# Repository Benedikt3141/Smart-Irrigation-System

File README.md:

→ Current Version as .step Assembly ([Assembly](src/assembly_and_models/SmartIrrigationSystem-Assembly.step)

# About

The Smart Irrigation System is a battery-powered monitoring and control system for watering up to six individual plants.

Each plant is monitored by a capacitive soil moisture sensor connected to the main control unit.

The project currently focuses on the main monitoring and control unit. A separate watering unit is planned but not fully designed yet. Communication between both units is intended to use ESP-NOW.

## Project Overview

The system consists of two main parts:

### Main Monitoring and Control Unit

The main unit collects sensor data, displays current measurements on a TFT screen, logs data to an SD card and indicates the system status using an LED strip.

Each soil moisture sensor is connected individually using an audio jack connector.

### Watering Unit

The watering unit is planned as a separate module. It will receive commands from the main control unit via ESP-NOW and control the water flow using a solenoid valve.
The unit should also monitor the water tank level using an ultrasonic sensor.

This part of the system is still work in progress. But It will be bareable with electronic modules I have at hand so I won't need a custom PCB for it and it also doesn't count to the sponsorship.

## Feature overview

###### Sensors (Inputs)

- **Soil mositure monitoring** for individual plants
- **Temperature**
- Humidity
- Air pressure
- Air Quality
- CO2 concentration
- Solar intensity
- 3 Buttons
- *Tank fill state sensor*

###### Other features and outputs

- **Battery powered**
- 3.2" TFT LCD Screen with resistive touch
- Buzzer
- SD log with data saved as .csv
- LED-Strip status indicator
- Lighting for the Buttons
- magnetic valve for watering Control
- *web interface*
- *Push Emails when water is empty/error etc.*

   → Version one of this project (didn't completely work)

## Repository Structure

This repository contains both the firmware and the PCB design files.

- `/firmware/` contains the PlatformIO firmware project.
- `/firmware/src/` contains the ESP32 source code.
- `/src/pcb/` contains the KiCad PCB design files.
- `/src/pcb/Smart_Irrigation_SystemV2/production/` contains the exported Gerber files for manufacturing.
- `/src/pcb/assembly_and_models` contains 3d assembly files

## File Structure

```
Smart-Irrigation-System/
├── firmware/
├── images/
├── src/│  
│   ├── assembly_and_models/
│   │   ├── SmartIrrigationSystem-Assembly.step
│   │   └── SmartIrrigationSystem.FCStd
│   └── pcb/
│       └── Smart_Irrigation_SytemV2/
├── .gitignore
├── BOM.csv
├── Concept.jpg
├── JOURNAL.md
├── LICENSE
├── README.md
├── cart_adafruit.png
├── cart_amazon.png
└── cart_jlcpcb.png
```

## Getting started

#### Requirements

To work with this project, you need:

* VS Code
* PlatformIO or pioarduino IDE Extension
* C++ Compiler
* KiCad 10.0.1 or later
* You also need a 3D printer with Filament you want to use for printing the housing and other regular hardware tools like a soldering iron 

#### Installation

Use git to clone this repository into your computer.

```
git clone https://github.com/Benedikt3141/Smart-Irrigation-System.git
```

Open the project folder in VS Code and build/upload the firmware using PlatformIO or pioarduino IDE.

###### Hardware

You can either use the provided Gerber files or modify the KiCad project and generate new manufacturing files for your preferred PCB supplier.

You can find the gerberfiles for JLCPCB [here ](src/pcb/Smart_Irrigation_SystemV2/production). The correlating `BOM.csv` and `position.csv` can be found in the same directories.

## License

[MIT](https://choosealicense.com/licenses/mit/)

## Current Project Status

This project is still in development.

The main monitoring unit is mostly implemented. The watering unit, web interface and notification system are planned but not finished yet.

## Sources

[MQ2 Library](https://github.com/labay11/MQ-2-sensor-library/)
[SD Card](https://RandomNerdTutorials.com/esp32-web-server-microsd-card/)

## Why I think I should receive financial sponsorship for this project

I already received $180 in rewards from Hack Club in July 2026. Since then, I have spent nearly 100 hours working on this project. During this time, I have gained many new skills and a lot of knowledge in PCB design, including effective routing techniques, reading datasheets, organizing schematics, and working with Git. I have also developed personal skills, especially resilience and perseverance throughout this long process.

I started this project seven months ago, and I'm still determined to bring it to completion. Even though I've had to pause my work several times because I'm still in school, have exams coming up in two years, and have many other hobbies and responsibilities that take up my free time, I've always found a way to keep making progress.

I've carefully reviewed and checked my design multiple times, and I'm now quite confident that the hardware design is ready to be finalized.

I'm really proud of what I've accomplished and everything I've learned along the way. This project has been a challenging but incredibly rewarding experience, and I'm excited to take the next step toward completing it.

Thank you, Hack Club, for supporting my previous request. I would be very grateful if you could help me with this next chapter of my project! I need 500$ (450€) to finance this the new pcb (SmartIrrigationSystemV2.5) and the other neccessary parts mentioned in the BOM like Displays, fans, buttons, LEDs etc.. The rest of the money I'll need for this project iteration I'll pay from my own money.

## AI Usage

All of the code was written by myself. Since this is a work in progress, the code may still contain bugs or parts that could be improved.

The PCB design, hardware architecture and  the firmware were
created completely by myself.

## Bill of Materials (BOM)

| Item                                                            | Qty | Unit price | Total price | Purchase link                                                  | Notes                                                      |
| ----------------------------------------------------------------- | ----: | -----------: | ------------: | ---------------------------------------------------------------- | ------------------------------------------------------------ |
| PCB_Board                                                       |   1 |       15€ |        15€ |[Product](cart_jlcpcb.png)                                                             | —                                                         |
| PCB_Assembly                                                    |   1 |      186€ |       186€ | [Product](cart_jlcpcb.png)                                                            | —                                                         |
| PCB Shipping and Taxes                                          |   1 |      100€ |       100€ | [Product](cart_jlcpcb.png)                                                             | Last time I ordered, I had to pay 60€ tax before delivery |
| Nocuta NF-A6x15 5V PWM                                          |   1 |       17€ |        17€ | [Product](https://www.amazon.de/dp/B0DJP3987K?tag=noctua09-21) | Fan                                                        |
| 3.2 TFT Display with Resistive Touchscreen                      |   2 |       15€ |        30€ | [Product](https://www.adafruit.com/product/4278)               | Touchscreen                                                |
| Kailh Mechanical Key Switches - Tactile Brown - 10-pack WS2812B |   1 |        7€ |         7€ | [Product](https://www.adafruit.com/product/4954)               | Switches                                                   |
| NeoPixel Nano 2020 RGB LEDs -10-Pack -WS2812B                   |   1 |        4€ |         4€ | [Product](https://www.adafruit.com/product/4684)               | LEDs for under the switches                                |
| NeoPixel Stick -8 x 5050 RGBW LEDs -WarmWhite ~3000K            |   2 |        8€ |        16€ | [Product](https://www.adafruit.com/product/2867)               | LEDs for under the board                                   |
| Translucent Keycaps for MX Compatible Switches - 10 pack        |   1 |        5€ |         5€ | [Product](https://www.adafruit.com/product/4956)               | Keycaps                                                    |
| Lithium Ion Polymer Battery - 3.7v 2500mAh                      |   1 |       15€ |        15€ | [Product](https://www.adafruit.com/product/328)                | LiPo                                                       |
| SoilMoisture Sensors 6pcs                      |   1 |       9€ |        9€ | [Product](https://www.amazon.de/Aideepen-Bodenfeuchtigkeitssensor-Hygrometer-Modul-korrosionsbest%C3%A4ndiges-Arduin0-Pflanzenbew%C3%A4sserung/dp/B08GCRZVSR/ref=sr_1_4?s=industrial)                | Moisture sensors                                                        |
| Shipping                                                        |   1 |       50€ |        50€ | —                                                             | Shipping from Adafruit and Amazon                          |

**Total: 454 €**

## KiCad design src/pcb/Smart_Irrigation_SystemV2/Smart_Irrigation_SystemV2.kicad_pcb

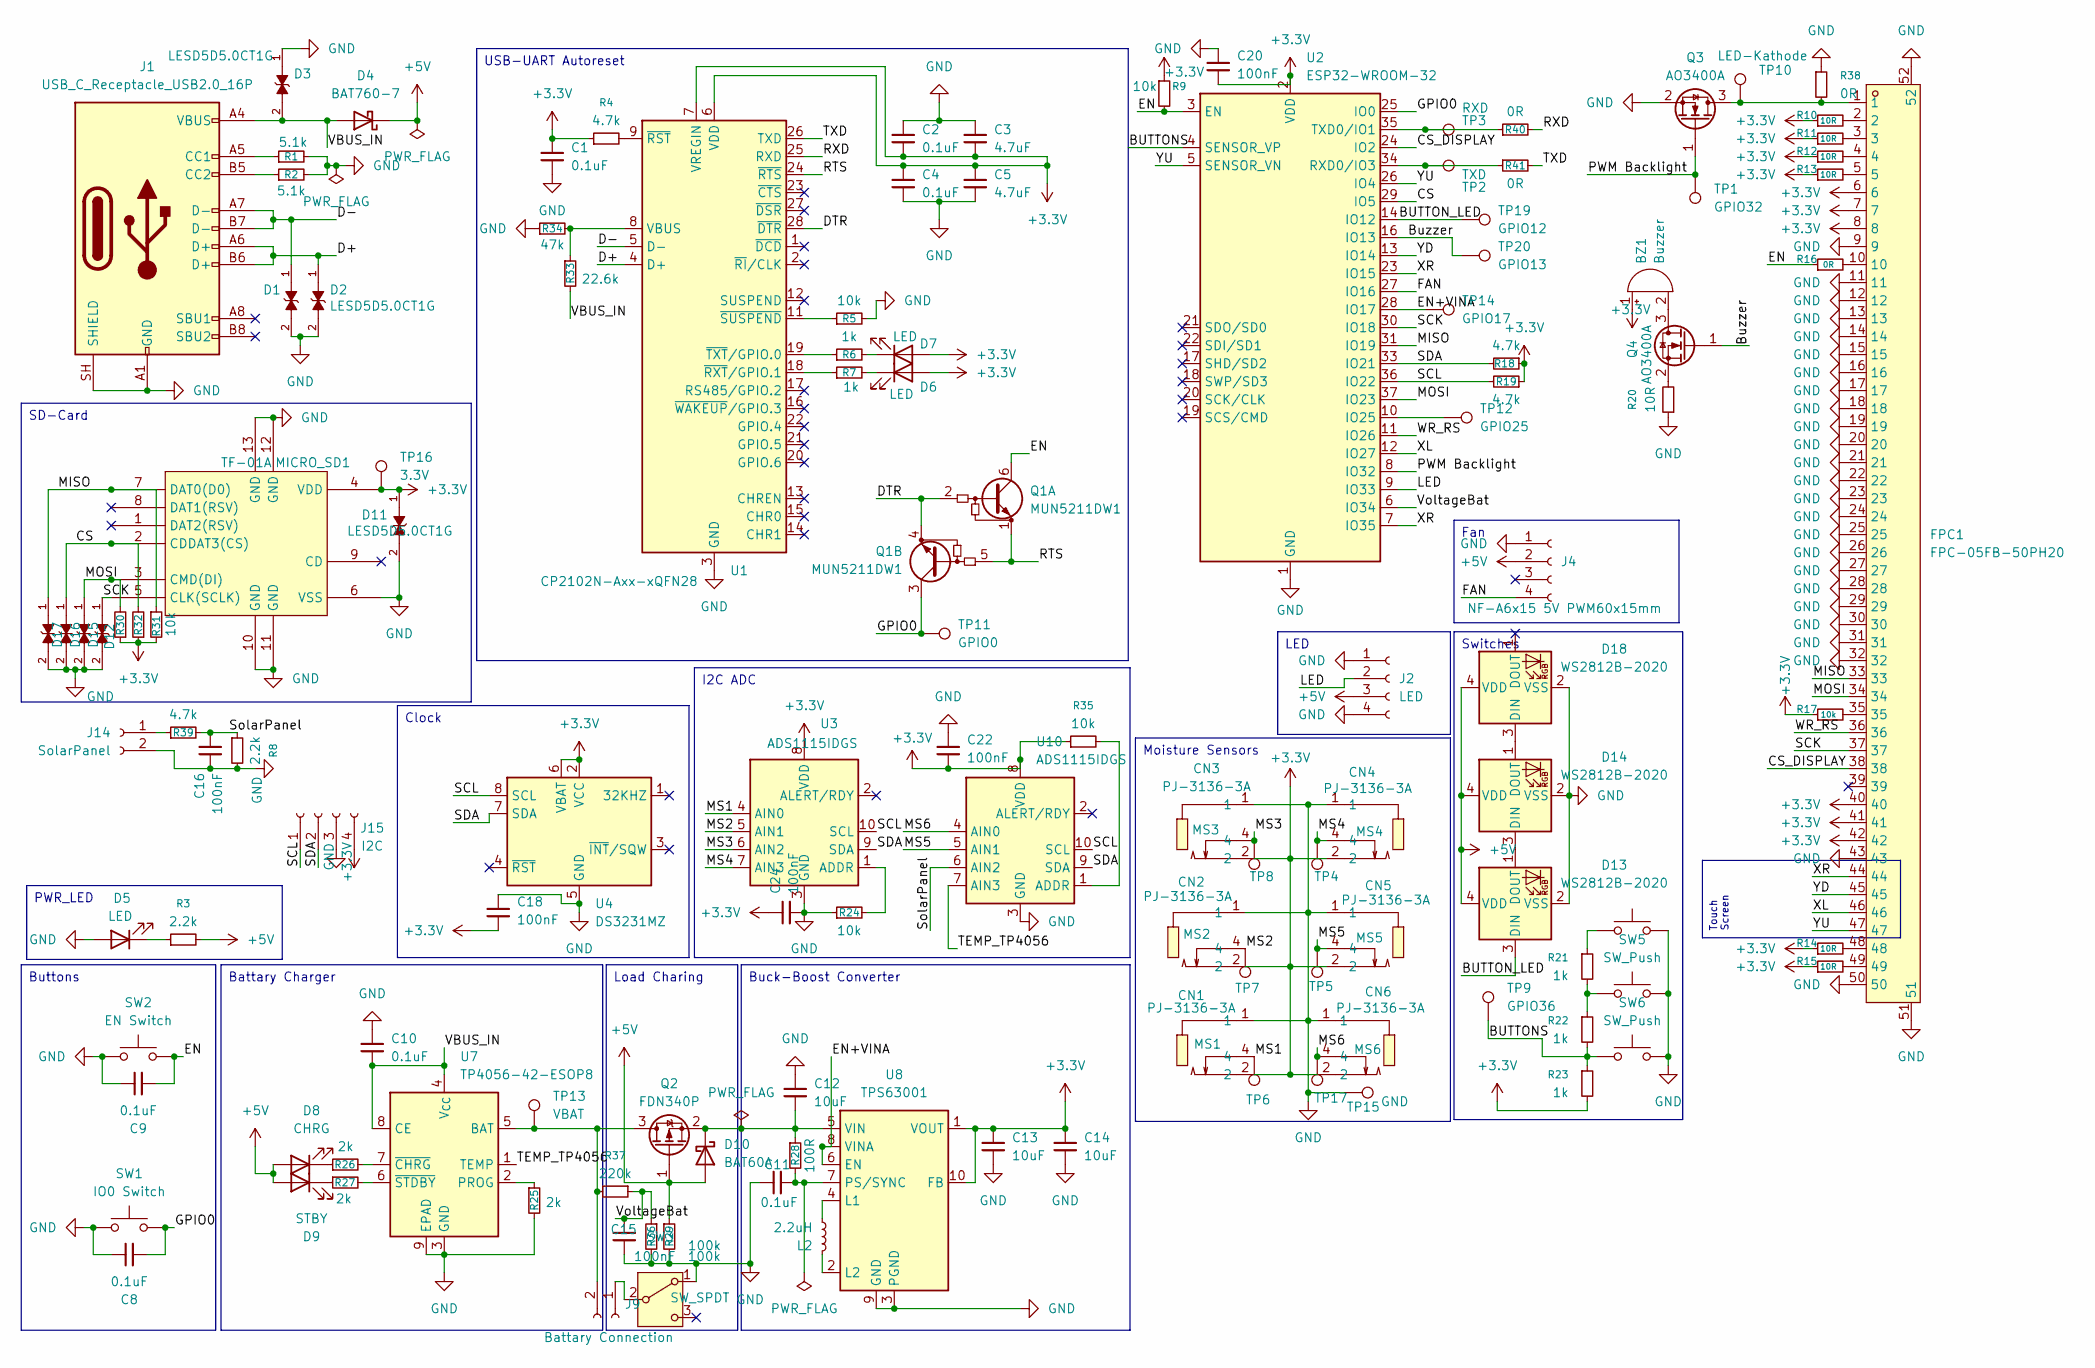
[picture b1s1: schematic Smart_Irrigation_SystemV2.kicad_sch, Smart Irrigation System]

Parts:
BZ1: Buzzer; BUZ-TH_BD12.0-P6.50-D0.6-FD; JLCPCB Part Number C968749
C1, C2, C4, C8, C9, C10, C11: 0.1uF; C_0805_2012Metric; JLCPCB Part Number C28233
C3, C5: 4.7uF; C_0805_2012Metric; JLCPCB Part Number C1779
C12, C13, C14: 10uF; C_0805_2012Metric; JLCPCB Part Number C15850
C15, C16, C18, C20, C22, C24: 100nF; C_0805_2012Metric; JLCPCB Part Number C29926
CN1, CN2, CN3, CN4, CN5, CN6: PJ-3136-3A; AUDIO-TH_PJ-3136-3A; MPN PJ-3136-3A; LCSC Part C707248
D1, D2, D3, D11, D12, D15, D16, D17: LESD5D5.0CT1G; TVS_LESD5D5.0CT1G; PARTREV O; JLCPCB Part Number C5274290
D4: BAT760-7; D_SOD-323; JLCPCB Part Number C27636120
D5, D6, D7: LED; D_0603_1608Metric; JLCPCB Part Number C2286
D8: CHRG; D_0603_1608Metric; JLCPCB Part Number C2287
D9: STBY; D_0603_1608Metric; JLCPCB Part Number C12624
D10: BAT60A; D_SOD-323; JLCPCB Part Number C513277
D13, D14, D18: WS2812B-2020; LED_WS2812B-2020_PLCC4_2.0x2.0mm
FPC1: FPC-05FB-50PH20; FPC-SMD_50P-P0.50_FPC-05FB-50PH20; MPN FPC-05FB-50PH20; LCSC Part C2856838
J1: USB_C_Receptacle_USB2.0_16P; USB_C_Receptacle_HCTL_HC-TYPE-C-16P-01A; JLCPCB Part Number C5337088
J2: LED; PinSocket_1x04_P2.54mm_Vertical
J4: NF-A6x15 5V PWM60x15mm; PinSocket_1x04_P2.54mm_Vertical
J9: Battary Connection; JST_PH_B2B-PH-K_1x02_P2.00mm_Vertical
J14: SolarPanel; JST_PH_B2B-PH-K_1x02_P2.00mm_Vertical
J15: I2C; PinSocket_1x04_P2.54mm_Vertical
L2: 2.2uH; IND-SMD_L6.6-W6.6; JLCPCB Part Number C128686
MICRO_SD1: TF-01A; TF-SMD_TF-01A; MPN TF-01A; JLCPCB Part Number C91145
Q1: MUN5211DW1; SOT-363_SC-70-6; JLCPCB Part Number C152507
Q2: FDN340P; SOT-23; JLCPCB Part Number C347510
Q3, Q4: AO3400A; SOT-23; JLCPCB Part Number C20917
R1, R2: 5.1k; R_0805_2012Metric; JLCPCB Part Number C26023
R3, R8: 2.2k; R_0805_2012Metric; JLCPCB Part Number C17520
R4, R18, R19, R39: 4.7k; R_0805_2012Metric; JLCPCB Part Number C17673
R5, R9, R17, R24, R30, R31, R32, R35: 10k; R_0805_2012Metric; JLCPCB Part Number C17414
R6, R7, R21, R22, R23: 1k; R_0805_2012Metric; JLCPCB Part Number C17513
R10, R11, R12, R13, R14, R15, R20: 10R; R_0805_2012Metric; JLCPCB Part Number C17415
R16, R38: 0R; R_0805_2012Metric; JLCPCB Part Number C17477
R25, R26, R27: 2k; R_0805_2012Metric; JLCPCB Part Number C17604
R28: 100R; R_0805_2012Metric; JLCPCB Part Number C17408
R29, R36: 100k; R_0805_2012Metric; JLCPCB Part Number C25611
R33: 22.6k; R_0805_2012Metric; JLCPCB Part Number C12825
R34: 47k; R_0805_2012Metric; JLCPCB Part Number C17713
R37: 220k; R_0805_2012Metric; JLCPCB Part Number C17556
R40, R41: 0R; R_1206_3216Metric; JLCPCB Part Number C17888
SW1: IO0 Switch; KEY-SMD_4P-L6.0-W6.0-P3.90-LS9.0; JLCPCB Part Number C83206
SW2: EN Switch; KEY-SMD_4P-L6.0-W6.0-P3.90-LS9.0; JLCPCB Part Number C83206
SW3: SW_SPDT; SW_100SP1T1B1M1QEH
SW4, SW5, SW6: SW_Push; KEY-TH_CPG1511F01S0X
TP1: GPIO32; TestPoint_Pad_D1.5mm
TP2: TXD; TestPoint_Pad_D1.5mm
TP3: RXD; TestPoint_Pad_D1.5mm
TP4: MS4; TestPoint_Pad_D1.5mm
TP5: MS5; TestPoint_Pad_D1.5mm
TP6: MS1; TestPoint_Pad_D1.5mm
TP7: MS2; TestPoint_Pad_D1.5mm
TP8: MS3; TestPoint_Pad_D1.5mm
TP9: GPIO36; TestPoint_Pad_D1.5mm
TP10: LED-Kathode; TestPoint_Pad_D1.5mm
TP11: GPIO0; TestPoint_Pad_D1.5mm
TP12: GPIO25; TestPoint_Pad_D1.0mm
TP13: VBAT; TestPoint_Pad_D1.5mm
TP14: GPIO17; TestPoint_Pad_D1.0mm
TP15: GND; TestPoint_Pad_2.5x2.5mm
TP16: 3.3V; TestPoint_Pad_2.5x2.5mm
TP17: MS6; TestPoint_Pad_D1.5mm
TP19: GPIO12; TestPoint_Pad_D1.0mm
TP20: GPIO13; TestPoint_Pad_D1.0mm
U1: CP2102N-Axx-xQFN28; QFN-28-1EP_5x5mm_P0.5mm_EP3.35x3.35mm; JLCPCB Part Number C964632
U2: ESP32-WROOM-32; JLCPCB Part Number C701343
U3, U10: ADS1115IDGS; TSSOP-10_3x3mm_P0.5mm; JLCPCB Part Number C37593
U4: DS3231MZ; SOIC-8_3.9x4.9mm_P1.27mm; JLCPCB Part Number C107410
U7: TP4056-42-ESOP8; SOIC-8-1EP_3.9x4.9mm_P1.27mm_EP2.41x3.3mm_ThermalVias; JLCPCB Part Number C16581
U8: TPS63001; Texas_DRC0010J_ThermalVias; JLCPCB Part Number C28060

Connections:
+3.3V: BZ1.1 (+), C1.1, C2.2, C3.2, C4.1, C5.1, C13.1, C14.1, C18.2, C20.2, C22.2, C24.1, CN1.2, CN2.2, CN3.2, CN4.2, CN5.2, CN6.2, D6.2 (A), D7.2 (A), D11.1, FPC1.6, FPC1.7, FPC1.8, FPC1.40, FPC1.41, FPC1.42, J15.4, MICRO_SD1.4 (VDD), R4.1, R9.1, R10.1, R11.1, R12.1, R13.1, R14.1, R15.1, R17.1, R18.1, R19.1, R23.2, R30.1, R31.2, R32.1, R35.1, TP16.1 (1_1), U1.6 (VDD), U1.7 (VREGIN), U2.2 (VDD), U3.8 (VDD), U4.2 (VCC), U4.6 (VBAT), U8.1 (VOUT), U8.10 (FB), U10.8 (VDD)
+5V: D4.1 (K), D8.2 (A), D9.2 (A), D10.2 (A), D13.4 (VDD), D14.4 (VDD), D18.4 (VDD), J2.3, J4.2, Q2.1 (G), R3.2, R29.1
/BUTTONS: R22.2, R23.1, SW6.1, TP9.1 (1_1), U2.4 (SENSOR_VP)
/BUTTON_LED: D13.3 (DIN), TP19.1 (1_1), U2.14 (IO12)
/Buzzer: Q4.1 (G), TP20.1 (1_1), U2.16 (IO13)
/CS: D16.1, MICRO_SD1.2 (CDDAT3(CS)), R32.2, U2.29 (IO5)
/CS_DISPLAY: FPC1.38, U2.24 (IO2)
/D+: D2.1, J1.A6 (D+), J1.B6 (D+), U1.4 (D+)
/D-: D1.1, J1.A7 (D-), J1.B7 (D-), U1.5 (D-)
/DTR: Q1.2 (B1), Q1.4 (E2), U1.28 (~DTR)
/EN: C9.2, Q1.6 (C1), R9.2, R16.1, SW2.2, U2.3 (EN)
/EN+VINA: TP14.1 (1_1), U2.28 (IO17), U8.6 (EN), U8.8 (VINA)
/FAN: J4.4, U2.27 (IO16)
/GPIO0: C8.2, Q1.3 (C2), SW1.2, TP11.1 (1_1), U2.25 (IO0)
/LED: J2.2, U2.9 (IO33)
/MISO: D17.1, FPC1.33, MICRO_SD1.7 (DAT0(D0)), R31.1, U2.31 (IO19)
/MOSI: D15.1, FPC1.34, MICRO_SD1.3 (CMD(DI)), R30.2, U2.37 (IO23)
/MS1: CN1.4, TP6.1 (1_1), U3.4 (AIN0)
/MS2: CN2.4, TP7.1 (1_1), U3.5 (AIN1)
/MS3: CN3.4, TP8.1 (1_1), U3.6 (AIN2)
/MS4: CN4.4, TP4.1 (1_1), U3.7 (AIN3)
/MS5: CN5.4, TP5.1 (1_1), U10.5 (AIN1)
/MS6: CN6.4, TP17.1 (1_1), U10.4 (AIN0)
/PWM Backlight: Q3.1 (G), TP1.1 (1_1), U2.8 (IO32)
/RTS: Q1.1 (E1), Q1.5 (B2), U1.24 (~RTS)
/RXD: R40.2, U1.25 (RXD)
/SCK: D12.1, FPC1.37, MICRO_SD1.5 (CLK(SCLK)), U2.30 (IO18)
/SCL: J15.1, R19.2, U2.36 (IO22), U3.10 (SCL), U4.8 (SCL), U10.10 (SCL)
/SDA: J15.2, R18.2, U2.33 (IO21), U3.9 (SDA), U4.7 (SDA), U10.9 (SDA)
/SolarPanel: C16.1, R8.1, R39.2, U10.6 (AIN2)
/TEMP_TP4056: U7.1 (TEMP), U10.7 (AIN3)
/TXD: R41.2, U1.26 (TXD)
/VBUS_IN: C10.2, D3.2, D4.2 (A), J1.A4 (VBUS), J1.A9 (VBUS), J1.B4 (VBUS), J1.B9 (VBUS), R33.2, U7.4 (V_{CC}), U7.8 (CE)
/VoltageBat: C15.1, R36.1, R37.1, U2.6 (IO34)
/WR_RS: FPC1.36, U2.11 (IO26)
/XL: FPC1.46, U2.12 (IO27)
/XR: FPC1.44, U2.7 (IO35), U2.23 (IO15)
/YD: FPC1.45, U2.13 (IO14)
/YU: FPC1.47, U2.5 (SENSOR_VN), U2.26 (IO4)
GND: C1.2, C2.1, C3.1, C4.2, C5.2, C8.1, C9.1, C10.1, C11.1, C12.1, C13.2, C14.2, C15.2, C16.2, C18.1, C20.1, C22.1, C24.2, CN1.1, CN2.1, CN3.1, CN4.1, CN5.1, CN6.1, D1.2, D2.2, D3.1, D5.2 (A), D11.2, D12.2, D13.2 (VSS), D14.2 (VSS), D15.2, D16.2, D17.2, D18.2 (VSS), FPC1.9, FPC1.11, FPC1.12, FPC1.13, FPC1.14, FPC1.15, FPC1.16, FPC1.17, FPC1.18, FPC1.19, FPC1.20, FPC1.21, FPC1.22, FPC1.23, FPC1.24, FPC1.25, FPC1.26, FPC1.27, FPC1.28, FPC1.29, FPC1.30, FPC1.31, FPC1.32, FPC1.43, FPC1.50, FPC1.51, FPC1.52, J1.A1 (GND), J1.A12 (GND), J1.B1 (GND), J1.B12 (GND), J1.SH (SHIELD), J2.1, J2.4, J4.1, J14.2, J15.3, MICRO_SD1.6 (VSS), MICRO_SD1.10 (GND), MICRO_SD1.11 (GND), MICRO_SD1.12 (GND), MICRO_SD1.13 (GND), Q3.2 (S), R1.2, R2.2, R5.2, R8.2, R20.1, R24.1, R25.2, R29.2, R34.1, R36.2, R38.1, SW1.1, SW2.1, SW3.1 (A), SW4.2, SW5.2, SW6.2, TP15.1 (1_1), U1.3 (GND), U1.29 (GND), U2.1 (GND), U2.15 (GND), U2.38 (GND), U2.39 (GND), U3.3 (GND), U4.5 (GND), U7.3 (GND), U7.9 (EPAD), U8.3 (PGND), U8.9 (GND), U8.11 (PGND), U10.3 (GND)
unnamed: BZ1.2 (-), Q4.3 (D)
unnamed: D5.1 (K), R3.1
unnamed: D6.1 (K), R7.2
unnamed: D7.1 (K), R6.2
unnamed: D8.1 (K), R26.1
unnamed: D9.1 (K), R27.1
unnamed: C12.2, D10.1 (K), Q2.2 (S), R28.1, U8.5 (VIN)
unnamed: D13.1 (DOUT), D14.3 (DIN)
unnamed: D14.1 (DOUT), D18.3 (DIN)
unnamed: FPC1.2, R10.2
unnamed: FPC1.3, R11.2
unnamed: FPC1.4, R12.2
unnamed: FPC1.5, R13.2
unnamed: FPC1.10, R16.2
unnamed: FPC1.35, R17.2
unnamed: FPC1.48, R14.2
unnamed: FPC1.49, R15.2
unnamed: J1.A5 (CC1), R1.1
unnamed: J1.B5 (CC2), R2.1
unnamed: J9.1, SW3.2 (B)
unnamed: J9.2, Q2.3 (D), R37.2, TP13.1 (1_1), U7.5 (BAT)
unnamed: J14.1, R39.1
unnamed: FPC1.1, Q3.3 (D), R38.2, TP10.1 (1_1)
unnamed: Q4.2 (S), R20.2
unnamed: R21.1, SW4.1
unnamed: R21.2, R22.1, SW5.1
unnamed: R33.1, R34.2, U1.8 (VBUS)
unnamed: R4.2, U1.9 (~RST)
unnamed: R7.1, U1.18 (~RXT/GPIO.1)
unnamed: R5.1, U1.11 (~SUSPEND)
unnamed: R6.1, U1.19 (~TXT/GPIO.0)
unnamed: TP12.1 (1_1), U2.10 (IO25)
unnamed: R41.1, TP2.1 (1_1), U2.34 (RXD0/IO3)
unnamed: R40.1, TP3.1 (1_1), U2.35 (TXD0/IO1)
unnamed: R24.2, U3.1 (ADDR)
unnamed: R25.1, U7.2 (PROG)
unnamed: R26.2, U7.7 (~CHRG)
unnamed: R27.2, U7.6 (~STDBY)
unnamed: L2.1, U8.4 (L1)
unnamed: L2.2, U8.2 (L2)
unnamed: C11.2, R28.2, U8.7 (PS/SYNC)
unnamed: R35.2, U10.1 (ADDR)

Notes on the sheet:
USB-UART Autoreset
Battary Charger
Clock
PWR_LED
LED
Buck-Boost Converter
Switches
Touch Screen
Buttons
Moisture Sensors
I2C ADC
Fan
SD-Card
Load Charing

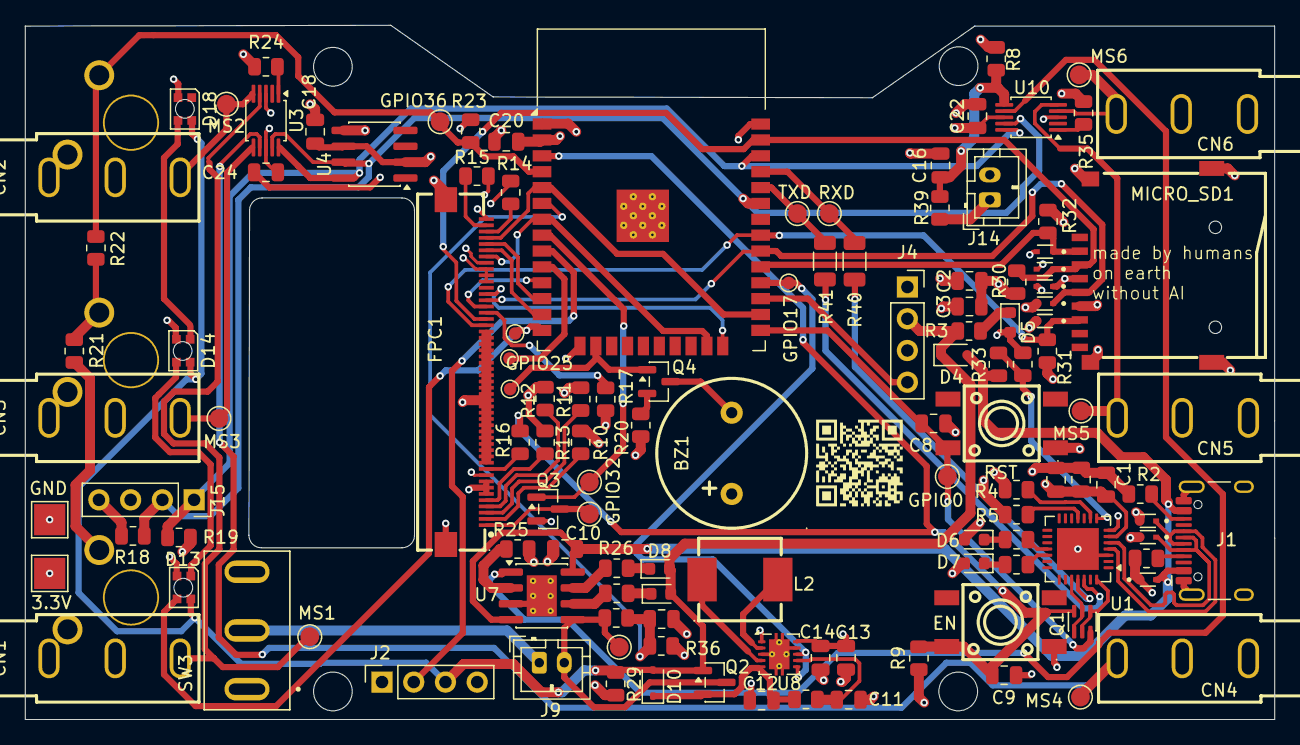
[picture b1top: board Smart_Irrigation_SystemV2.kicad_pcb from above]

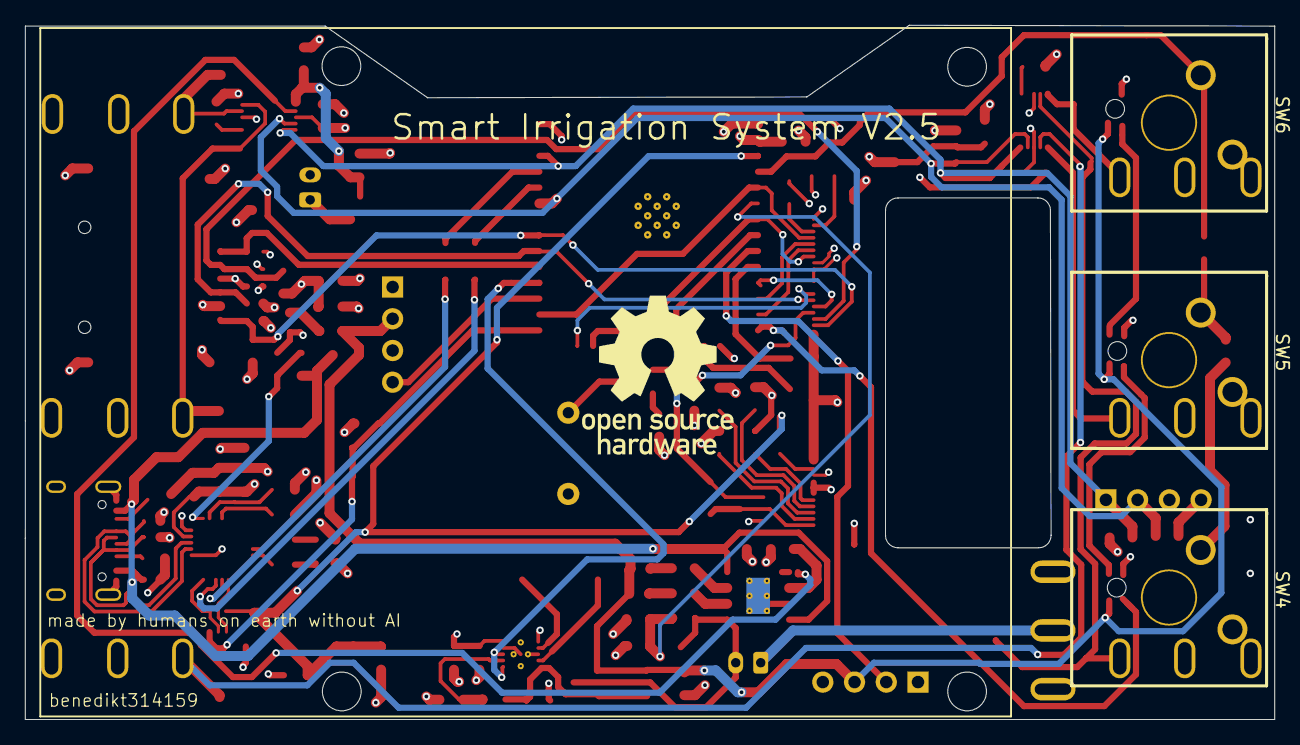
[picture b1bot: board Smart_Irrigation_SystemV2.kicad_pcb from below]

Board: 4 copper layers, 100.0 x 55.6 mm, 128 parts (3 on the bottom side), 82 nets.

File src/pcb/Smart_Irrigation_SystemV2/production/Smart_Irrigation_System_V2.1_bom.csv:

Designator,Footprint,Quantity,Value,LCSC Part #
"C1, C10, C11, C2, C4, C8, C9",0805,7,0.1uF,C28233
"C12, C13, C14",0805,3,10uF,C15850
"C15, C16, C18, C20, C21, C22, C23, C24",0805,8,100nF,C29926
"C3, C5, C6",0805,3,4.7uF,C1779
C7,0805,1,22uF,C45783
"CN1, CN2, CN3, CN4, CN5, CN6",AUDIO-TH_PJ-3136-3A,6,PJ-3136-3A,C707248
"D1, D11, D12, D15, D16, D17, D2, D3",TVS_LESD5D5.0CT1G,8,LESD5D5.0CT1G,C5274290
D10,D_SOD-323,1,BAT60A,C513277
D4,D_SOD-323F,1,BAT760-7,C27636120
"D5, D6, D7",0603,3,LED,C2286
D8,0603,1,CHRG,C2287
D9,0603,1,STBY,C12624
J1,USB_C_Receptacle_HCTL_HC-TYPE-C-16P-01A,1,USB_C_Receptacle_USB2.0_16P,C5337088
"J10, J11, J13, J15, J6",JST_EH_B4B-EH-A_1x04_P2.50mm_Vertical,5,I2C,
J14,JST_PH_B2B-PH-K_1x02_P2.00mm_Vertical,1,SolarPanel,
J16,PinSocket_1x04_P2.54mm_Vertical,1,GPIO_Expander,
J2,CON_5051105091_MOL,1,FPC_Connector,C779387
J9,JST_PH_B2B-PH-K_1x02_P2.00mm_Vertical,1,Battary Connection,
L1,IND-SMD_L7.1-W6.6,1,1uH,C726315
L2,IND-SMD_L6.6-W6.6,1,2.2uH,C128686
MICRO_SD1,TF-SMD_TF-01A,1,TF-01A,C91145
Q1,SOT-363_SC-70-6,1,MUN5211DW1,C152507
Q2,SOT-23,1,FDN340P,C347510
Q3,SOT-23,1,AO3400A,C20917
"R1, R2",0805,2,5.1k,C26023
"R10, R11, R12, R13, R14, R15",0805,6,10R,C17415
R16,0805,1,0R,C17477
"R17, R24, R30, R31, R32, R35, R5",0805,7,10k,C17414
"R18, R19, R39, R4",0805,4,4.7k,C17673
"R20, R21, R22, R23, R6, R7",0805,6,1k,C17513
"R25, R26, R27",0805,3,2k,C17604
R28,0805,1,100R,C17408
"R29, R36, R9",0805,3,100k,C25611
R3,0805,1,2.2k,C17520
R37,0805,1,220k,C17556
"R40, R41",1206,2,0R,C17888
R8,0805,1,453k,C17702
SW1,KEY-SMD_4P-L6.0-W6.0-P3.90-LS9.0,1,IO0 Switch,C83206
SW2,KEY-SMD_4P-L6.0-W6.0-P3.90-LS9.0,1,EN Switch,C83206
"SW3, SW4, SW5, SW6",SW_PUSH_6mm_H4.3mm,4,SW_Push,
TP1,TestPoint_Pad_D1.5mm,1,GPIO32,
TP10,TestPoint_Pad_D1.5mm,1,LED-Kathode,
TP11,TestPoint_Pad_D1.5mm,1,GPIO0,
TP13,TestPoint_Pad_D1.5mm,1,VBAT,
TP14,TestPoint_Pad_D1.5mm,1,GND,
TP15,TestPoint_Pad_2.5x2.5mm,1,GND,
TP16,TestPoint_Pad_4.0x4.0mm,1,3.3V,
TP17,TestPoint_Pad_D1.5mm,1,MS6,
TP18,TestPoint_Pad_D1.5mm,1,AnalogInput,
TP2,TestPoint_Pad_D1.5mm,1,TXD,
TP3,TestPoint_Pad_D1.5mm,1,RXD,
TP4,TestPoint_Pad_D1.5mm,1,MS4,
TP5,TestPoint_Pad_D1.5mm,1,MS5,
TP6,TestPoint_Pad_D1.5mm,1,MS1,
TP7,TestPoint_Pad_D1.5mm,1,MS2,
TP8,TestPoint_Pad_D1.5mm,1,MS3,
TP9,TestPoint_Pad_D1.5mm,1,GPIO36,
U1,QFN-28-1EP_5x5mm_P0.5mm_EP3.35x3.35mm,1,CP2102N-Axx-xQFN28,C964632 
"U10, U3",TSSOP-10_3x3mm_P0.5mm,2,ADS1115IDGS,C37593
U11,TSSOP-8_3x3mm_P0.65mm,1,PCA9536DP,C2649389
U2,ESP32-WROOM-32,1,ESP32-WROOM-32,C701343
U4,SOIC-8_3.9x4.9mm_P1.27mm,1,DS3231MZ,C107410
U5,SOT-563,1,TLV62568ADRL,C87122
U6,TSSOP-20_4.4x6.5mm_P0.65mm,1,SN74LVC245APW,C7848
U7,ESOP-8_L4.9-W3.9-P1.27-LS6.0-BL-EP,1,TP4056-42-ESOP8,C16581
U8,SOT-23-5,1,TPS63001,C28060

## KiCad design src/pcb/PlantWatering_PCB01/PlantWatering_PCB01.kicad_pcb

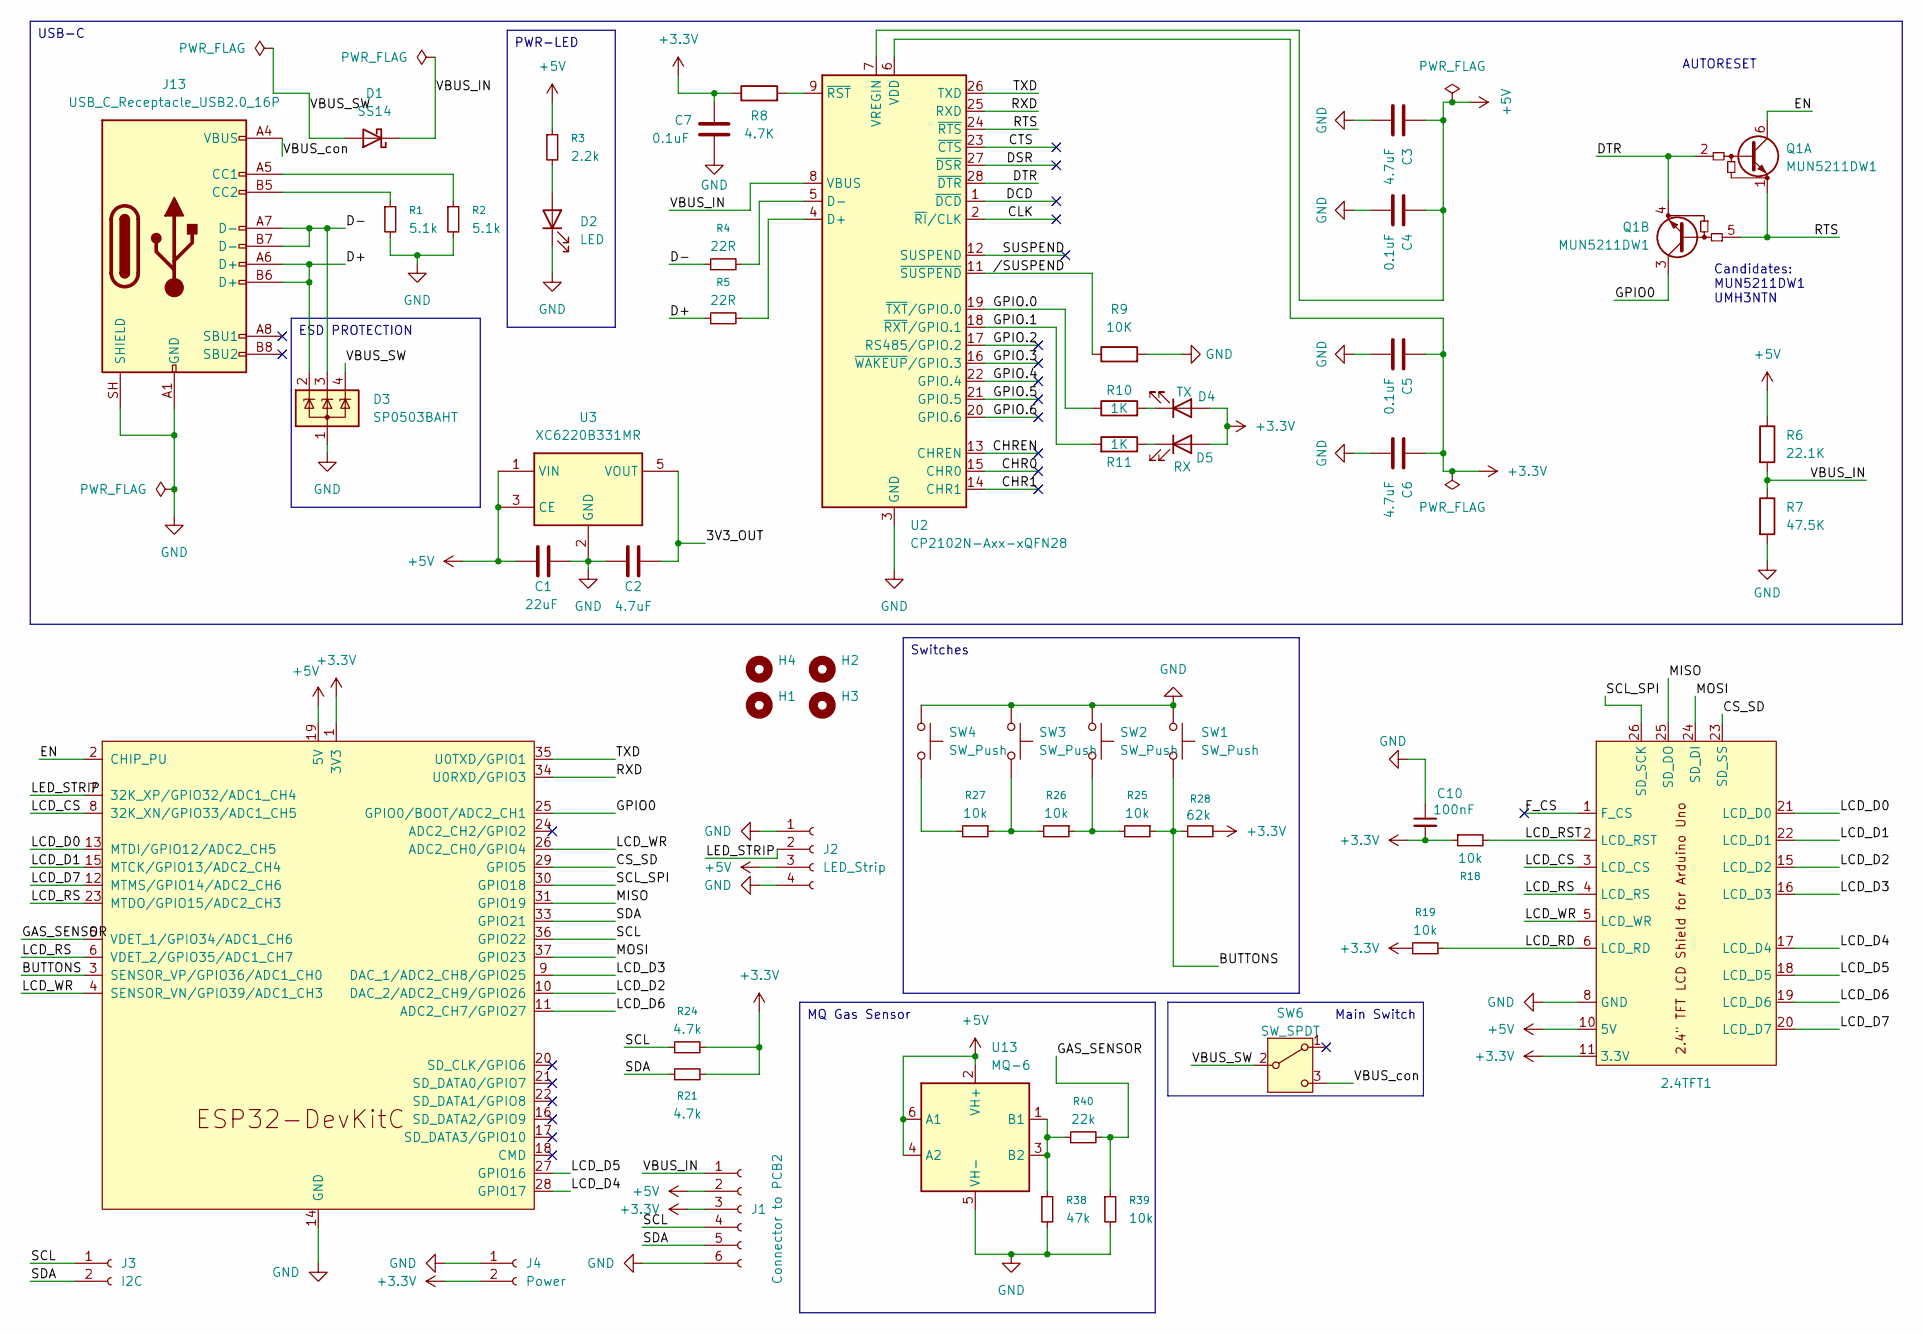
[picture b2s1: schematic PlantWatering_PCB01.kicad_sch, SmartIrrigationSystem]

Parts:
2.4TFT1: 2.4 TFT LCD Shield
C1: 22uF; C_1206_3216Metric; LCSC PN C5672
C2: 4.7uF; C_0805_2012Metric; LCSC PN C1779
C3, C6: 4.7uF; C_0805_2012Metric; Mouser PN GRM21BR71C475KE51L
C4, C5, C7: 0.1uF; C_0805_2012Metric; Mouser PN C0805C104K5RAC7411
C10: 100nF; C_0805_2012Metric; LCSC PN C28233
D1: SS14; D_SMA; LCSC PN C2480
D2: LED; LED_0603_1608Metric; LCSC PN C2286
D3: SP0503BAHT; SOT-143; LCSC PN C2682275
D4: TX; LED_0603_1608Metric; Mouser PN LTST-C170GKT
D5: RX; LED_0603_1608Metric; Mouser PN LTST-C170KFKT
H1, H2, H3, H4: MountingHole; MountingHole_3.2mm_M3
J1: Connector to PCB2; PinSocket_1x06_P2.00mm_Vertical
J2: LED_Strip; JST_PH_B4B-PH-K_1x04_P2.00mm_Vertical
J3: I2C; PinSocket_1x02_P2.00mm_Vertical
J4: Power; PinSocket_1x02_P2.00mm_Vertical
J13: USB_C_Receptacle_USB2.0_16P; USB_C_Receptacle_HRO_TYPE-C-31-M-12; LCSC PN C5337088
Q1: MUN5211DW1; SOT-363_SC-70-6; LCSC PN C152507
R1, R2: 5.1k; R_0805_2012Metric; LCSC PN C27834
R3: 2.2k; R_0805_2012Metric; LCSC PN C17520
R4, R5: 22R; R_0805_2012Metric; LCSC PN C17561
R6: 22.1K; R_0805_2012Metric; Mouser PN AC0805FR-0722K1L
R7: 47.5K; R_0805_2012Metric; Mouser PN AC0805FR-7W47K5L
R8: 4.7K; R_0805_2012Metric; Mouser PN AC0805FR-074K7L
R9: 10K; R_0805_2012Metric; Mouser PN AC0805FR-7W10KL
R10, R11: 1K; R_1206_3216Metric; Mouser PN AC0805FR-071KL
R18, R19, R25, R26, R27, R39: 10k; R_0805_2012Metric; LCSC PN C17414
R21, R24: 4.7k; R_0805_2012Metric; LCSC PN C17673
R28: 62k; R_0805_2012Metric; LCSC PN C17783
R38: 47k; R_0805_2012Metric; LCSC PN C17713
R40: 22k; R_0805_2012Metric; LCSC PN C17560
SW1, SW2, SW3, SW4: SW_Push; SW_PUSH_6mm
SW6: SW_SPDT; SW_CK_JS202011AQN_DPDT_Angled; LCSC PN C221662
U1: ESP32-DevKitC
U2: CP2102N-Axx-xQFN28; QFN-28-1EP_5x5mm_P0.5mm_EP3.35x3.35mm; LCSC PN C964632
U3: XC6220B331MR; SOT-23-5; LCSC PN C22466451
U13: MQ-6

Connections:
+3.3V: 2.4TFT1.11 (3.3V), C5.1, C6.1, C7.1, C10.2, D4.2 (A), D5.2 (A), J1.3, J4.2, R8.1, R18.1, R19.1, R21.2, R24.2, R28.2, U1.1 (3V3), U2.6 (VDD)
+5V: 2.4TFT1.10 (5V), C1.1, C3.1, C4.1, J1.2, J2.3, R3.1, R6.1, U1.19 (5V), U2.7 (VREGIN), U3.1 (VIN), U3.3 (CE), U13.2 (VH+), U13.4 (A2), U13.6 (A1)
/3V3_OUT: C2.2, U3.5 (VOUT)
/BUTTONS: R25.1, R28.1, SW1.2, U1.3 (SENSOR_VP/GPIO36/ADC1_CH0)
/CHR0: U2.15 (CHR0)
/CHR1: U2.14 (CHR1)
/CHREN: U2.13 (CHREN)
/CLK: U2.2 (~RI/CLK)
/CS_SD: 2.4TFT1.23 (SD_SS), U1.29 (GPIO5)
/CTS: U2.23 (~CTS)
/D+: D3.2 (K), J13.A6 (D+), J13.B6 (D+), R5.1
/D-: D3.3 (K), J13.A7 (D-), J13.B7 (D-), R4.1
/DCD: U2.1 (~DCD)
/DSR: U2.27 (~DSR)
/DTR: Q1.2 (B1), Q1.4 (E2), U2.28 (~DTR)
/EN: Q1.6 (C1), U1.2 (CHIP_PU)
/F_CS: 2.4TFT1.1 (F_CS)
/GAS_SENSOR: R39.1, R40.2, U1.5 (VDET_1/GPIO34/ADC1_CH6)
/GPIO0: Q1.3 (C2), U1.25 (GPIO0/BOOT/ADC2_CH1)
/GPIO.0: R10.1, U2.19 (~TXT/GPIO.0)
/GPIO.1: R11.2, U2.18 (~RXT/GPIO.1)
/GPIO.2: U2.17 (RS485/GPIO.2)
/GPIO.3: U2.16 (~WAKEUP/GPIO.3)
/GPIO.4: U2.22 (GPIO.4)
/GPIO.5: U2.21 (GPIO.5)
/GPIO.6: U2.20 (GPIO.6)
/LCD_CS: 2.4TFT1.3 (LCD_CS), U1.8 (32K_XN/GPIO33/ADC1_CH5)
/LCD_D0: 2.4TFT1.21 (LCD_D0), U1.13 (MTDI/GPIO12/ADC2_CH5)
/LCD_D1: 2.4TFT1.22 (LCD_D1), U1.15 (MTCK/GPIO13/ADC2_CH4)
/LCD_D2: 2.4TFT1.15 (LCD_D2), U1.10 (DAC_2/ADC2_CH9/GPIO26)
/LCD_D3: 2.4TFT1.16 (LCD_D3), U1.9 (DAC_1/ADC2_CH8/GPIO25)
/LCD_D4: 2.4TFT1.17 (LCD_D4), U1.28 (GPIO17)
/LCD_D5: 2.4TFT1.18 (LCD_D5), U1.27 (GPIO16)
/LCD_D6: 2.4TFT1.19 (LCD_D6), U1.11 (ADC2_CH7/GPIO27)
/LCD_D7: 2.4TFT1.20 (LCD_D7), U1.12 (MTMS/GPIO14/ADC2_CH6)
/LCD_RD: 2.4TFT1.6 (LCD_RD), R19.2
/LCD_RS: 2.4TFT1.4 (LCD_RS), U1.6 (VDET_2/GPIO35/ADC1_CH7), U1.23 (MTDO/GPIO15/ADC2_CH3)
/LCD_RST: 2.4TFT1.2 (LCD_RST), R18.2
/LCD_WR: 2.4TFT1.5 (LCD_WR), U1.4 (SENSOR_VN/GPIO39/ADC1_CH3), U1.26 (ADC2_CH0/GPIO4)
/LED_STRIP: J2.2, U1.7 (32K_XP/GPIO32/ADC1_CH4)
/MISO: 2.4TFT1.25 (SD_DO), U1.31 (GPIO19)
/MOSI: 2.4TFT1.24 (SD_DI), U1.37 (GPIO23)
/RTS: Q1.1 (E1), Q1.5 (B2), U2.24 (~RTS)
/RXD: U1.34 (U0RXD/GPIO3), U2.25 (RXD)
/SCL: J1.4, J3.1, R24.1, U1.36 (GPIO22)
/SCL_SPI: 2.4TFT1.26 (SD_SCK), U1.30 (GPIO18)
/SDA: J1.5, J3.2, R21.1, U1.33 (GPIO21)
/SUSPEND: U2.12 (SUSPEND)
/TXD: U1.35 (U0TXD/GPIO1), U2.26 (TXD)
/VBUS_IN: D1.1 (K), J1.1, R6.2, R7.1, U2.8 (VBUS)
/VBUS_SW: D1.2 (A), D3.4 (K), SW6.2 (B)
/VBUS_con: J13.A4 (VBUS), J13.A9 (VBUS), J13.B4 (VBUS), J13.B9 (VBUS), SW6.3 (C)
//SUSPEND: R9.1, U2.11 (~SUSPEND)
GND: 2.4TFT1.8 (GND), C1.2, C2.1, C3.2, C4.2, C5.2, C6.2, C7.2, C10.1, D2.1 (K), D3.1 (A), J1.6, J2.1, J2.4, J4.1, J13.A1 (GND), J13.A12 (GND), J13.B1 (GND), J13.B12 (GND), J13.SH (SHIELD), R1.2, R2.2, R7.2, R9.2, R38.2, R39.2, SW1.1, SW2.1, SW3.1, SW4.1, U1.14 (GND), U1.32 (GND), U1.38 (GND), U2.3 (GND), U2.29 (GND), U3.2 (GND), U13.5 (VH-)
unnamed: D2.2 (A), R3.2
unnamed: D4.1 (K), R10.2
unnamed: D5.1 (K), R11.1
unnamed: J13.A5 (CC1), R2.1
unnamed: J13.B5 (CC2), R1.1
unnamed: R25.2, R26.1, SW2.2
unnamed: R26.2, R27.1, SW3.2
unnamed: R27.2, SW4.2
unnamed: R5.2, U2.4 (D+)
unnamed: R4.2, U2.5 (D-)
unnamed: R8.2, U2.9 (~RST)
unnamed: R38.1, R40.1, U13.1 (B1), U13.3 (B2)

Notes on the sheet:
Candidates: MUN5211DW1 UMH3NTN
AUTORESET
Switches
USB-C
Main Switch
PWR-LED
MQ Gas Sensor
ESD PROTECTION

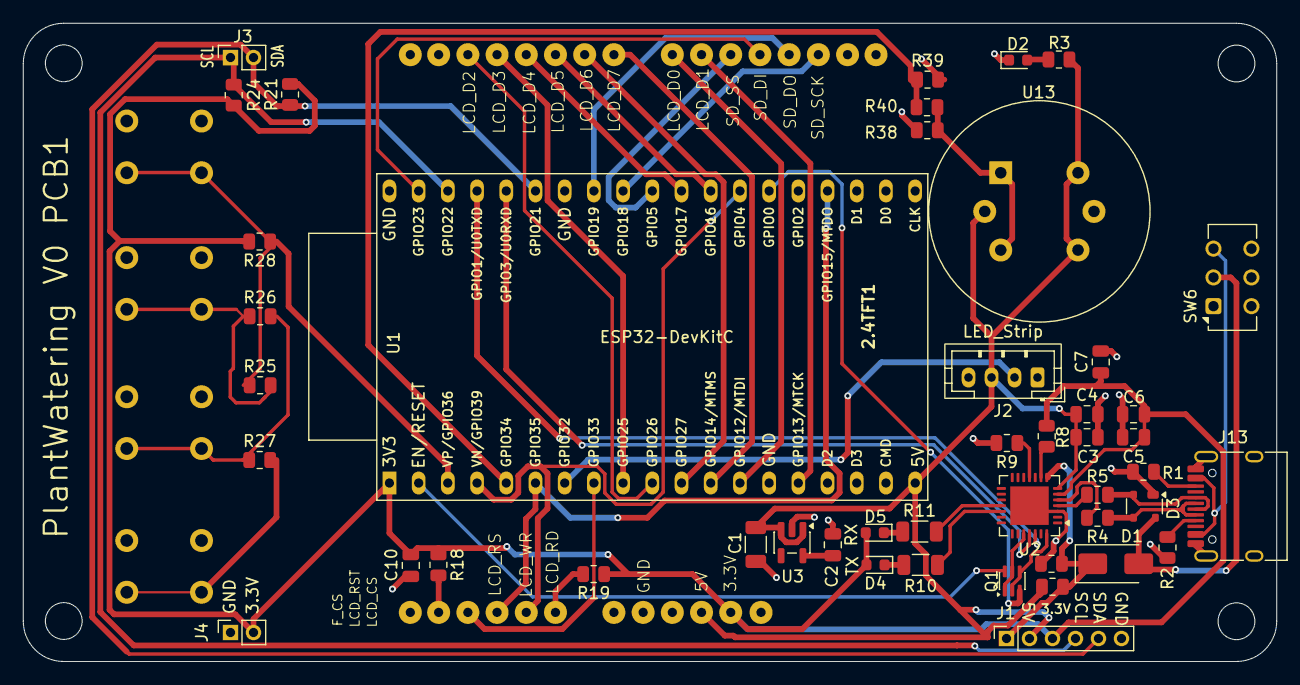
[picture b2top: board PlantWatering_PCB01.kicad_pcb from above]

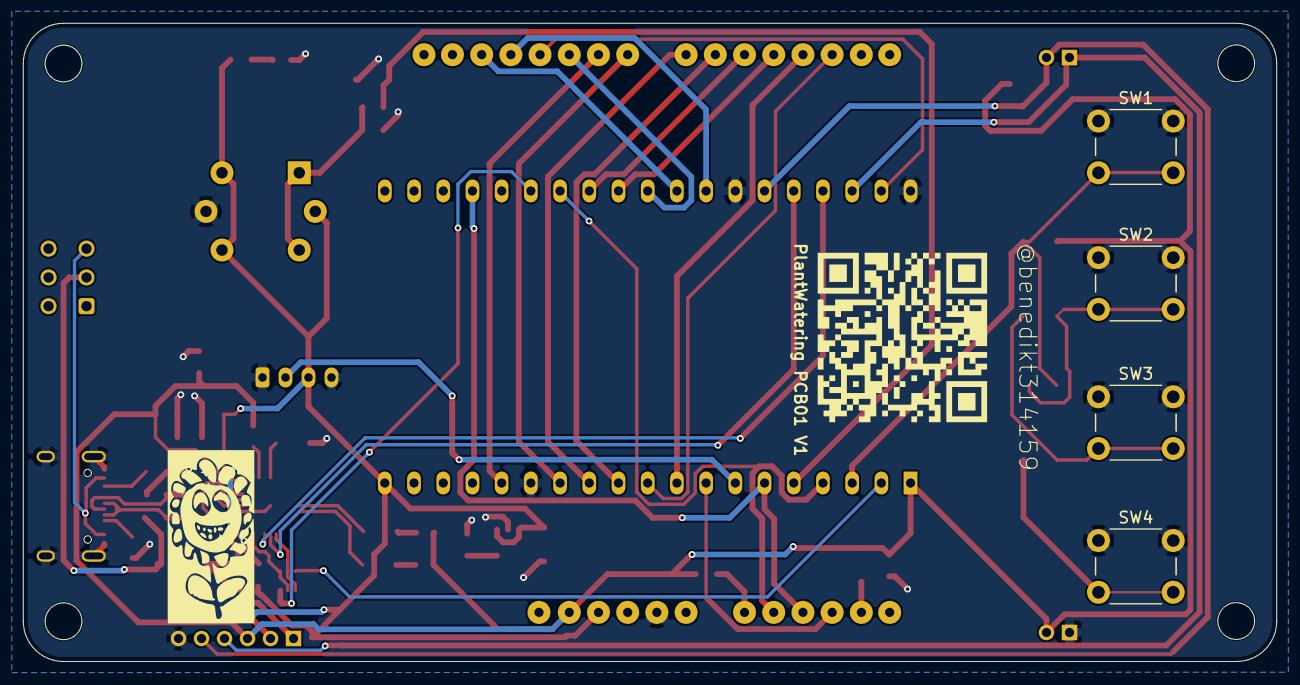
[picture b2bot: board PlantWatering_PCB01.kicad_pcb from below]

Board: 2 copper layers, 109.0 x 55.5 mm, 55 parts (4 on the bottom side), 52 nets.

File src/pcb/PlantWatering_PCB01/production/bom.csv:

Reference,Qty,Value,DNP,Exclude from BOM,Exclude from Board,Footprint,LCSC PN
C1,1,22uF,,,,Capacitor_SMD:C_1206_3216Metric,C5672
"C2,C3,C6",3,4.7uF,,,,Capacitor_SMD:C_0805_2012Metric,C1779
"C4,C5,C7",3,0.1uF,,,,Capacitor_SMD:C_0805_2012Metric,C28233
C10,1,100nF,,,,Capacitor_SMD:C_0805_2012Metric,C28233
D1,1,SS14,,,,Diode_SMD:D_SMA,C2480
D2,1,LED,,,,LED_SMD:LED_0603_1608Metric,C2286
D3,1,SP0503BAHT,,,,Package_TO_SOT_SMD:SOT-143,C2682275
D4,1,TX,,,,LED_SMD:LED_0603_1608Metric,C2286
D5,1,RX,,,,LED_SMD:LED_0603_1608Metric,C2286
J13,1,USB_C_Receptacle_USB2.0_16P,,,,Connector_USB:USB_C_Receptacle_HRO_TYPE-C-31-M-12,C5337088
Q1,1,MUN5211DW1,,,,Package_TO_SOT_SMD:SOT-363_SC-70-6,C152507
"R1,R2",2,5.1k,,,,Resistor_SMD:R_0805_2012Metric,C27834
R3,1,2.2k,,,,Resistor_SMD:R_0805_2012Metric,C17520
"R4,R5",2,22R,,,,Resistor_SMD:R_0805_2012Metric,C17561
R6,1,22.1K,,,,Resistor_SMD:R_0805_2012Metric,C17552
R7,1,47.5K,,,,Resistor_SMD:R_0805_2012Metric,C26011
R8,1,4.7K,,,,Resistor_SMD:R_0805_2012Metric,C17673
R9,1,10K,,,,Resistor_SMD:R_0805_2012Metric,C17414
"R10,R11",2,1K,,,,Resistor_SMD:R_1206_3216Metric,C1469
"R18,R19,R25,R26,R27,R39",6,10k,,,,Resistor_SMD:R_0805_2012Metric,C17414
"R21,R24",2,4.7k,,,,Resistor_SMD:R_0805_2012Metric,C17673
R28,1,62k,,,,Resistor_SMD:R_0805_2012Metric,C17783
R38,1,47k,,,,Resistor_SMD:R_0805_2012Metric,C17713
R40,1,22k,,,,Resistor_SMD:R_0805_2012Metric,C17560
SW6,1,SW_SPDT,,,,Button_Switch_THT:SW_CK_JS202011AQN_DPDT_Angled,C221662
U2,1,CP2102N-Axx-xQFN24,,,,Package_DFN_QFN:QFN-28-QFN-24-EP(4x4),C969151
U3,1,XC6220B331MR,,,,Package_TO_SOT_SMD:SOT-23-5,C22466451
